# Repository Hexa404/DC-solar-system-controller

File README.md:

# DC-solar-system-controller
specially for uav purpose. made as light as possible.

This project is a long term and open project, anyone can contribute. I'll make it private if i can get some money to realize it
The idea was making automatic cut off curent for balancing votltage of batteries that attached on uav
I'm not using discharger because its more simpler for me and I'm not going to waste any energy
schematic and code are uploaded soon and keep update until i make it private
.
.
.
#update
i change my mind, i use BMS instead switching it using relay so it not gonna use arduino
i might have to make an streaming device using raspberry pi and not using analog or digital fpv system

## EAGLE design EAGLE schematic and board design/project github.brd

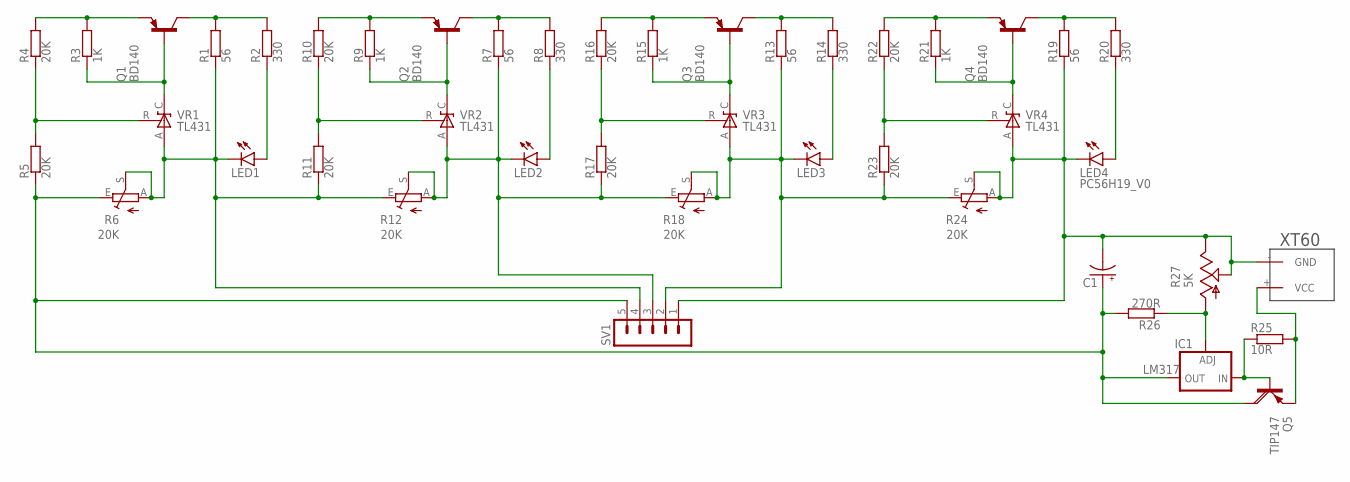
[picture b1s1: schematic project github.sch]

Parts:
C1: CPOL-US153CLV-0810; 153CLV-0810
IC1: LM317; DPACK
LED1, LED2, LED3, LED4: PC56H19_V0
Q1, Q2, Q3, Q4: BD140; TO126
Q5: TIP147; SOT93
R1, R7, R13, R19: 56; SMK
R2, R8, R14, R20: 330; SMK
R3, R9, R15, R21: 1K; SMK
R4, R5, R10, R11, R16, R17, R22, R23: 20K; SMK
R6, R12, R18, R24: 20K; RJ9W
R25: 10R; SMK
R26: 270R; SMK
R27: 5K; RJ9W
SV1: MA05-1
U$1: XT60
VR1, VR2, VR3, VR4: TL431; TO-92_RAC

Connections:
unnamed: Q1.1 (E), R3.1, R4.1
unnamed: R4.2, R5.1, VR1.R
unnamed: Q1.3 (B), R3.2, VR1.C
unnamed: Q1.2 (C), R1.1, R2.1
unnamed: LED1.1 (C), LED1.3 (C), R1.2, R6.A, R6.S, R11.2, R12.E, SV1.4, VR1.A
unnamed: R10.2, R11.1, VR2.R
unnamed: C1.+, IC1.4 (OUT), Q5.C, R5.2, R6.E, R26.1, SV1.5
unnamed: C1.-, LED4.1 (C), LED4.3 (C), R19.2, R24.A, R24.S, R27.E, R27.S, SV1.1, U$1.- (GND), VR4.A
unnamed: Q2.3 (B), R9.2, VR2.C
unnamed: Q2.1 (E), R9.1, R10.1
unnamed: Q2.2 (C), R7.1, R8.1
unnamed: LED2.1 (C), LED2.3 (C), R7.2, R12.A, R12.S, R17.2, R18.E, SV1.3, VR2.A
unnamed: IC1.1 (ADJ), R26.2, R27.A
unnamed: R16.2, R17.1, VR3.R
unnamed: Q3.3 (B), R15.2, VR3.C
unnamed: Q3.1 (E), R15.1, R16.1
unnamed: Q3.2 (C), R13.1, R14.1
unnamed: LED3.1 (C), LED3.3 (C), R13.2, R18.A, R18.S, R23.2, R24.E, SV1.2, VR3.A
unnamed: IC1.3 (IN), Q5.B, R25.2
unnamed: LED3.2 (A), LED3.4 (A), R14.2
unnamed: R22.2, R23.1, VR4.R
unnamed: Q4.3 (B), R21.2, VR4.C
unnamed: Q4.1 (E), R21.1, R22.1
unnamed: Q4.2 (C), R19.1, R20.1
unnamed: Q5.E, R25.1, U$1.+ (VCC)
unnamed: LED4.2 (A), LED4.4 (A), R20.2
unnamed: LED1.2 (A), LED1.4 (A), R2.2
unnamed: LED2.2 (A), LED2.4 (A), R8.2

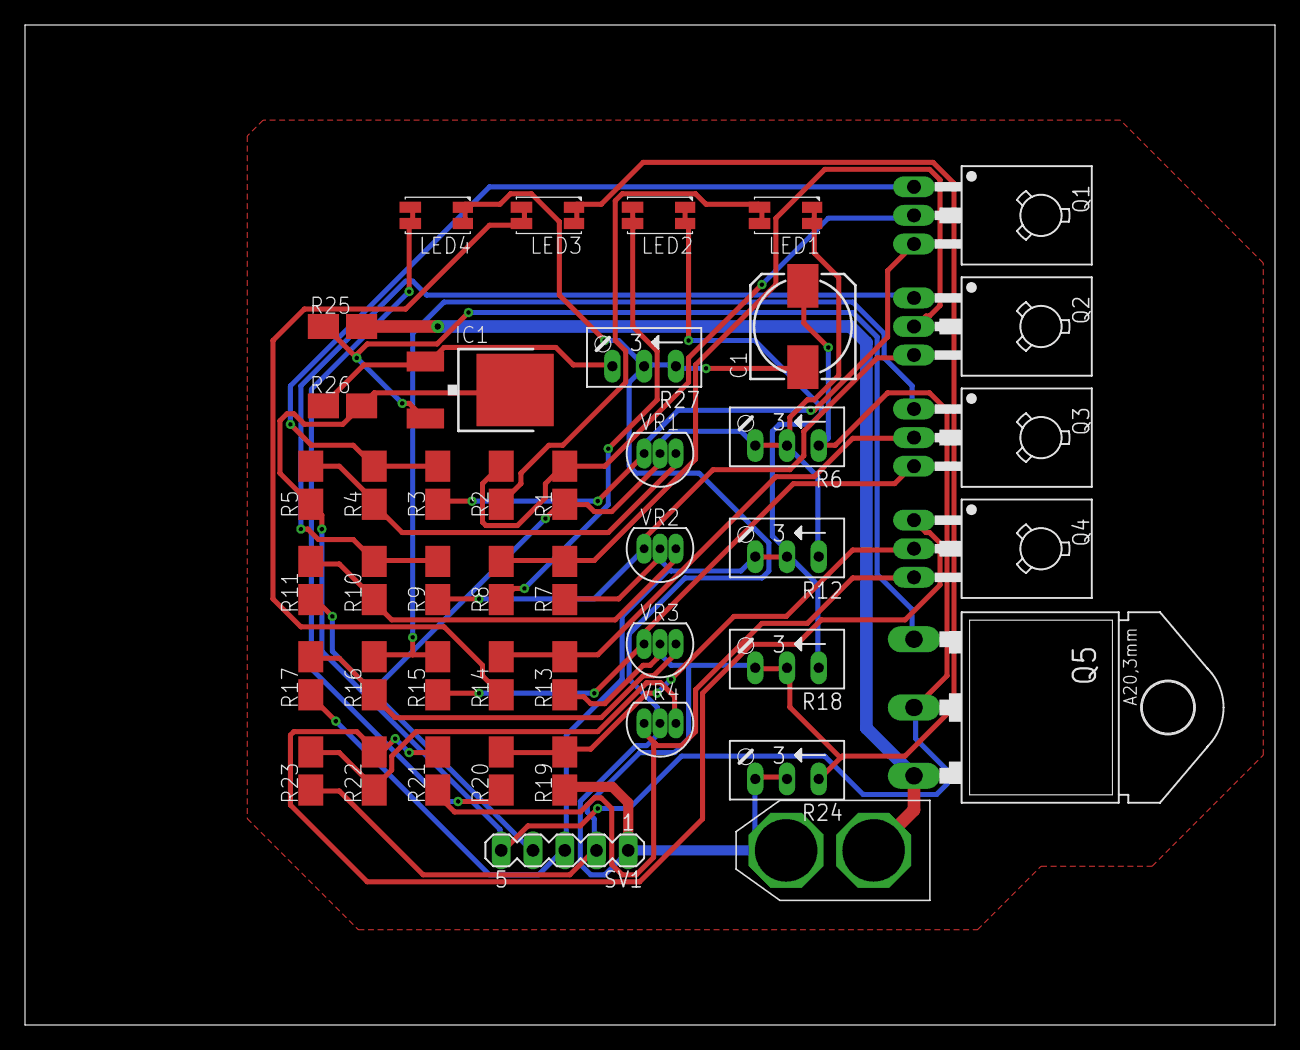
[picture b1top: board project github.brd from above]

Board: 2 copper layers, 100.0 x 80.0 mm, 44 parts (0 on the bottom side), 28 nets.

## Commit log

2021-08-28 Create uwu
2021-08-28 Rename project github.brd to EAGLE schematic and board design/project github.brd
2021-08-28 Rename EAGLE schematic and board designproject github.sch to EAGLE schematic and board design/project github.sch
